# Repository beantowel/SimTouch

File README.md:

# An attempt to make a Capacitive Touch Screen Stimulator

This project attempts to build a device which simulates human finger touch on a capacitive touch screen. We used two high-speed double diodes to build a switch which controls the connection between the conductive surface and the ground. If "the resistance be extremely high and the parasitic capacitance extremely low in the OFF state", then the induced equivalent capacitance would be very small, thus the touch screen won't detect it.

We built an array of these switches in a PCB, so we can use an MCU to control the stimulation in a 2-D plane.

By using PWM, we tried to reach higher resolution with limited conductive pads, since the area of these pads needs to be large to gain enough capacitance.

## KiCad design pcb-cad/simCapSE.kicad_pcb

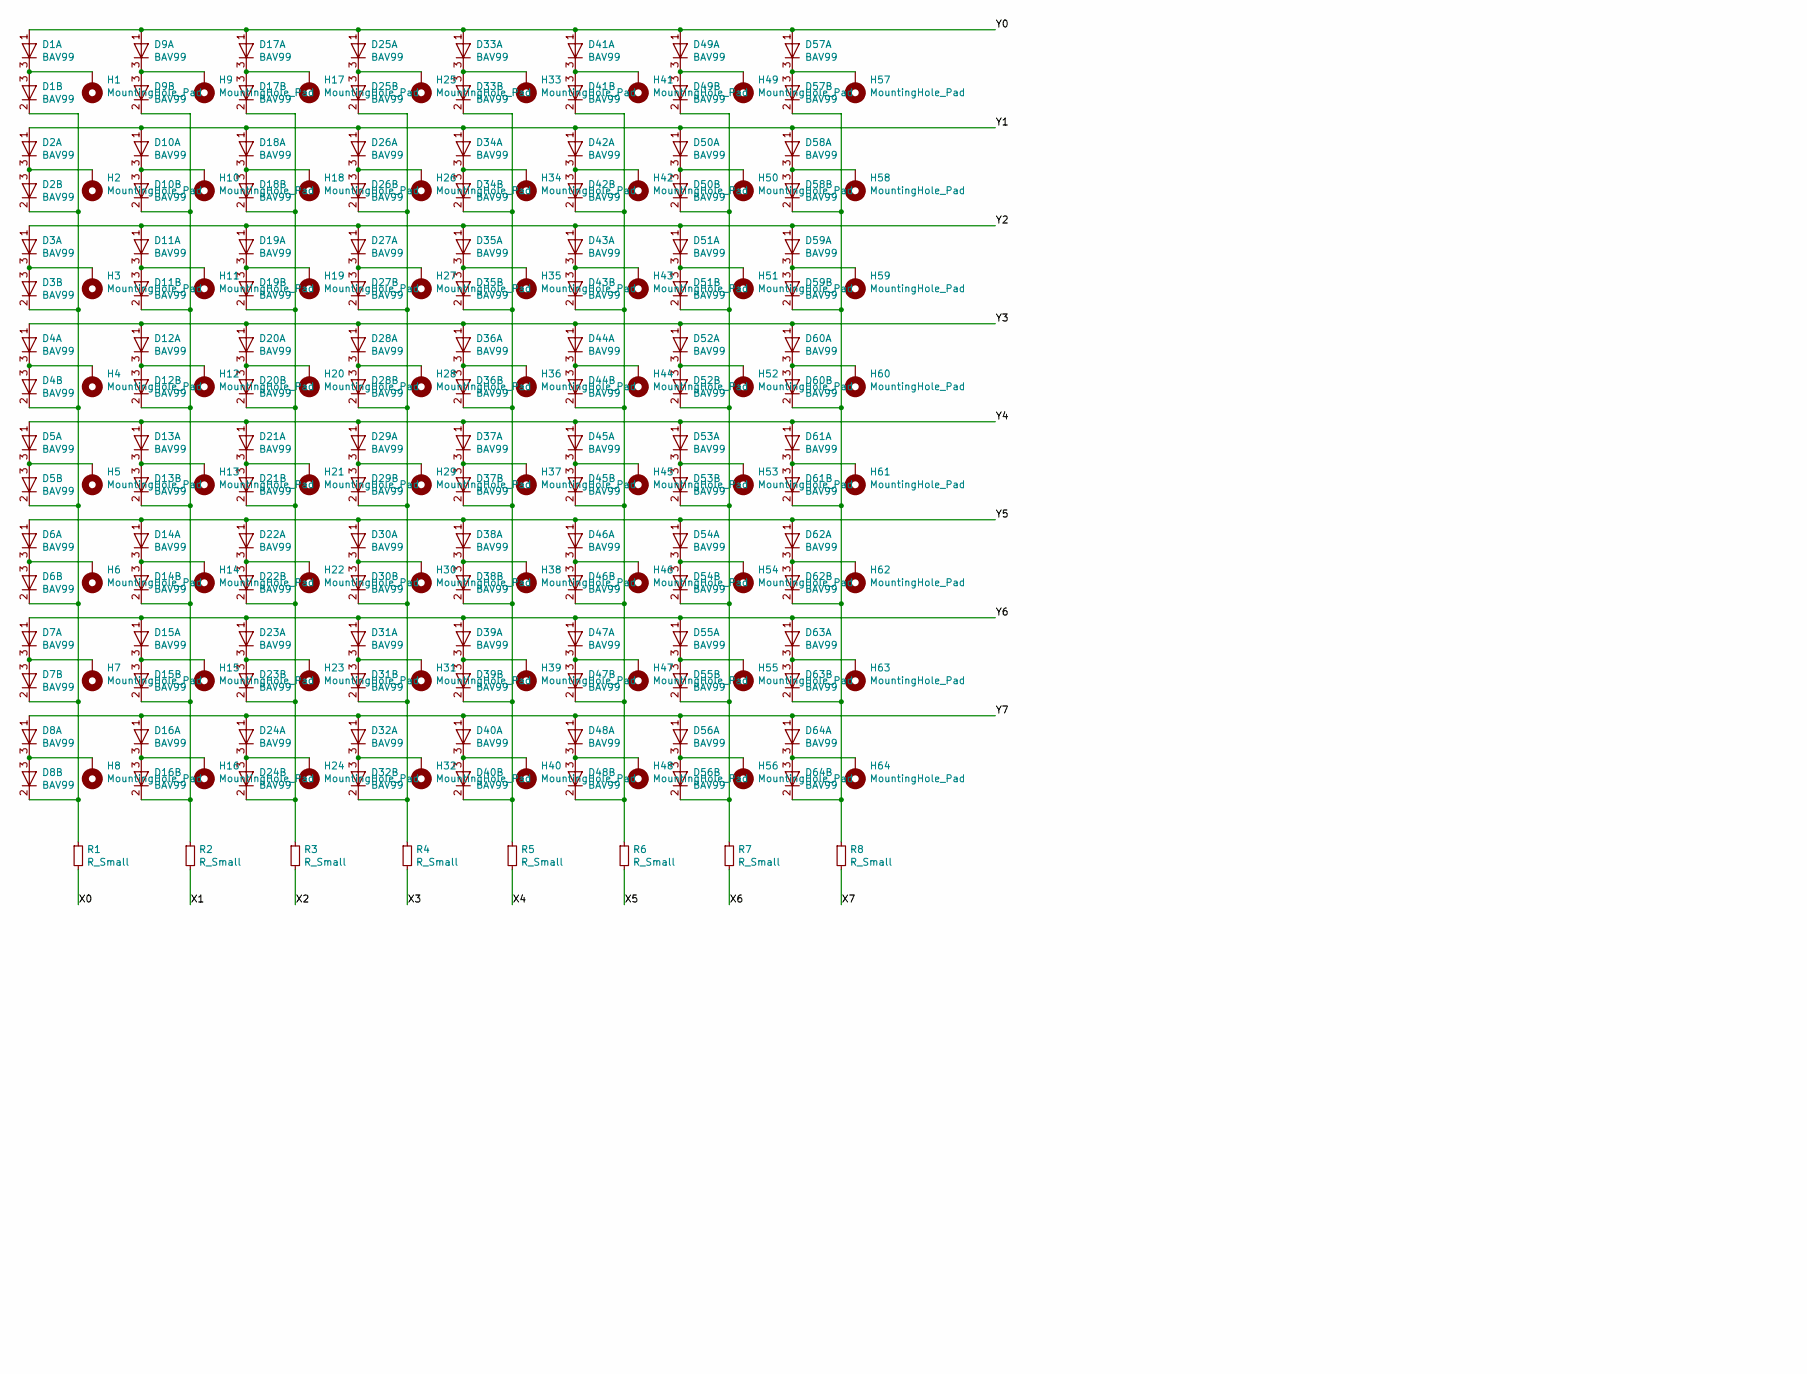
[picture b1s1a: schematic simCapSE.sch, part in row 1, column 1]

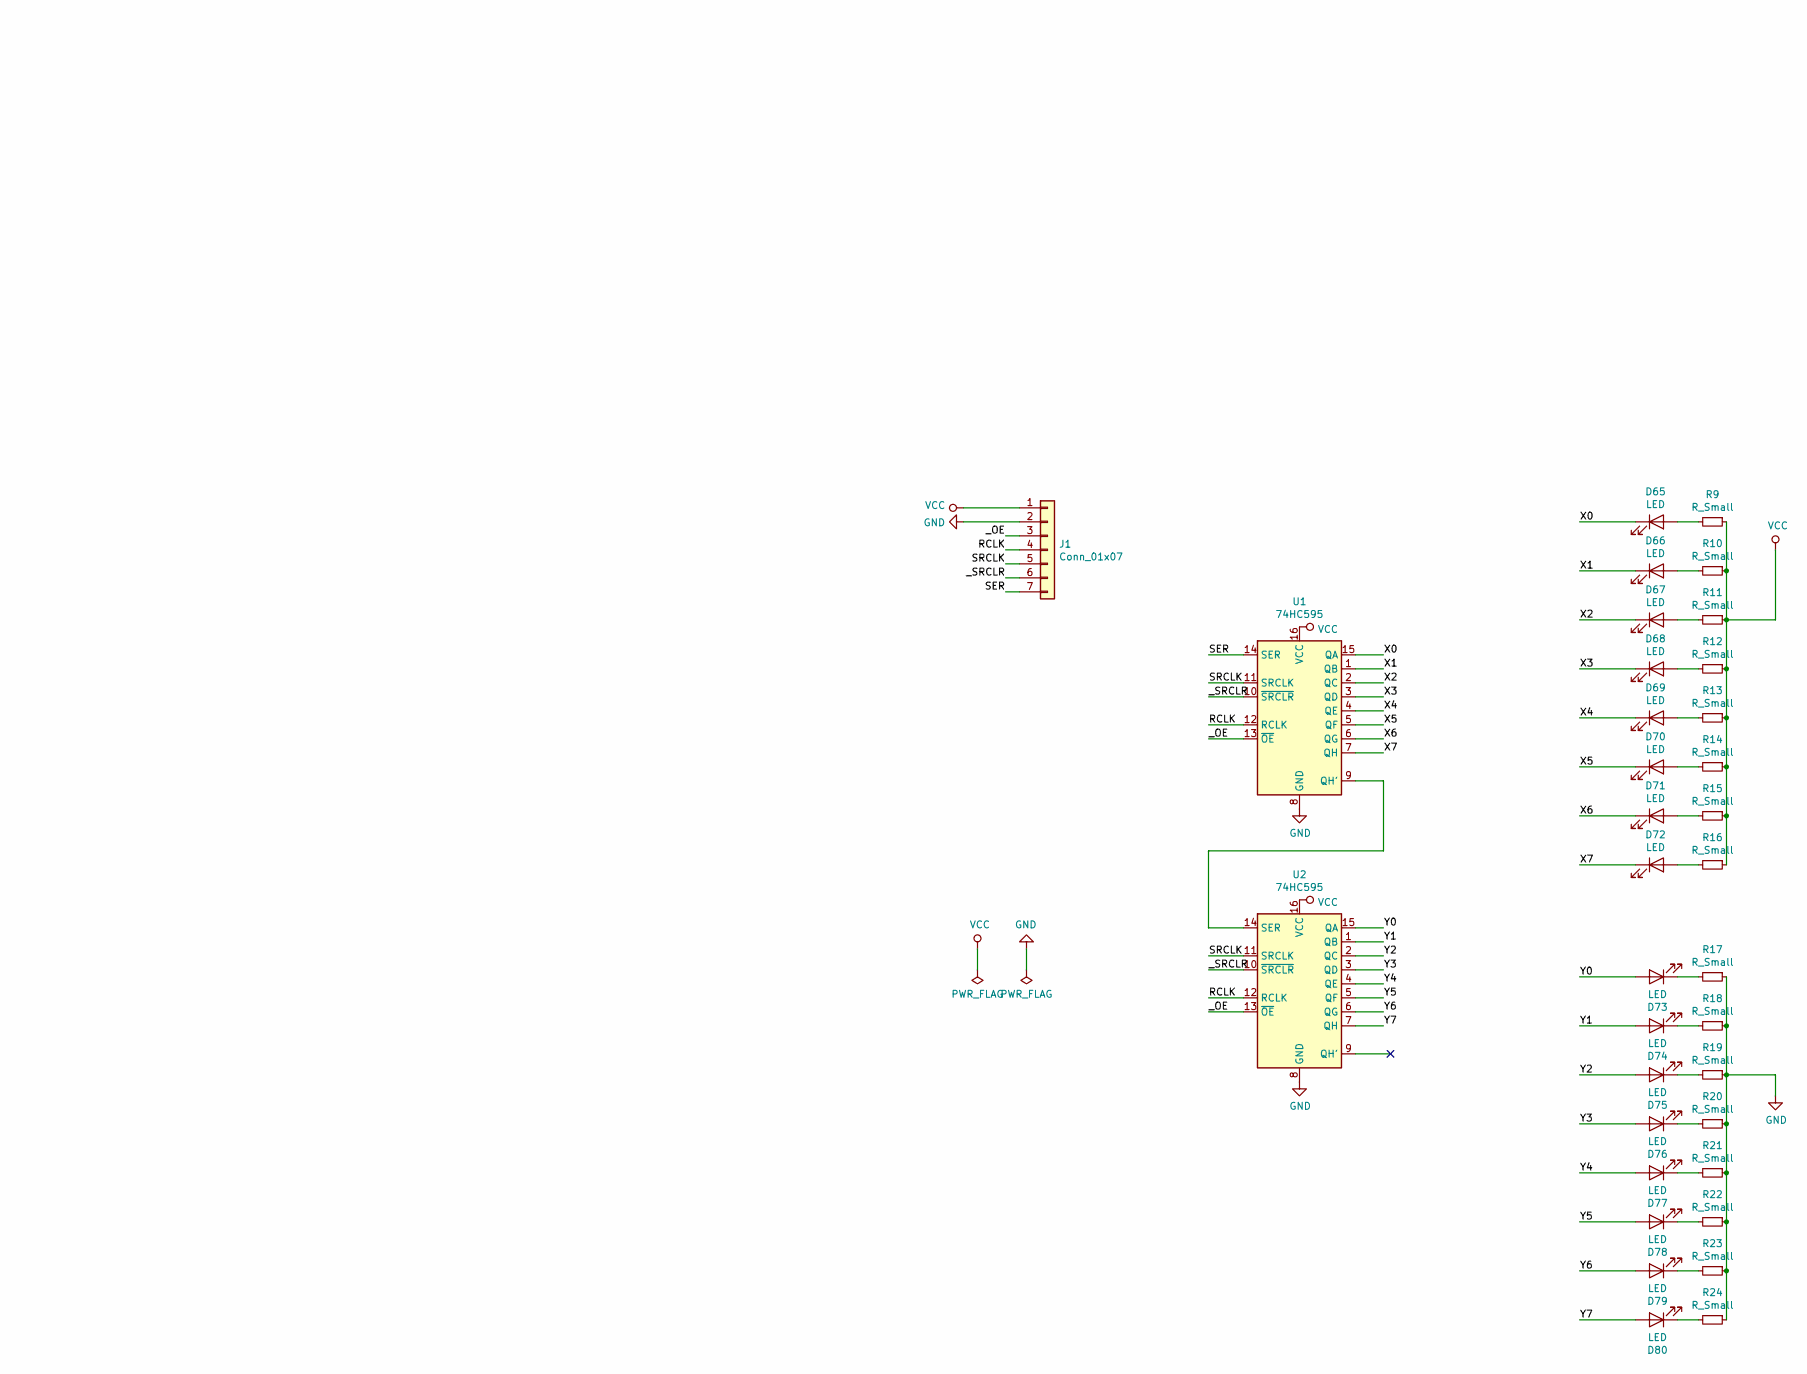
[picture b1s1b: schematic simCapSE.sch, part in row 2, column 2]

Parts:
D1, D2, D3, D4, D5, D6, D7, D8, D9, D10, D11, D12, D13, D14, D15, D16, D17, D18, D19, D20, D21, D22, D23, D24, D25, D26, D27, D28, D29, D30, D31, D32, D33, D34, D35, D36, D37, D38, D39, D40, D41, D42, D43, D44, D45, D46, D47, D48, D49, D50, D51, D52, D53, D54, D55, D56, D57, D58, D59, D60, D61, D62, D63, D64: BAV99; SOT-23
D65, D66, D67, D68, D69, D70, D71, D72, D73, D74, D75, D76, D77, D78, D79, D80: LED; LED_0805_2012Metric_Pad1.15x1.40mm_HandSolder
H1, H2, H3, H4, H5, H6, H7, H8, H9, H10, H11, H12, H13, H14, H15, H16, H17, H18, H19, H20, H21, H22, H23, H24, H25, H26, H27, H28, H29, H30, H31, H32, H33, H34, H35, H36, H37, H38, H39, H40, H41, H42, H43, H44, H45, H46, H47, H48, H49, H50, H51, H52, H53, H54, H55, H56, H57, H58, H59, H60, H61, H62, H63, H64: MountingHole_Pad; TCH_PAD
J1: Conn_01x07; PinHeader_1x07_P2.54mm_Horizontal
R1, R2, R3, R4, R5, R6, R7, R8, R9, R10, R11, R12, R13, R14, R15, R16, R17, R18, R19, R20, R21, R22, R23, R24: R_Small; R_0805_2012Metric_Pad1.15x1.40mm_HandSolder
U1, U2: 74HC595; SOP-16_4.55x10.3mm_P1.27mm

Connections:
/RCLK: J1.4, U1.12 (RCLK), U2.12 (RCLK)
/SER: J1.7, U1.14 (SER)
/SRCLK: J1.5, U1.11 (SRCLK), U2.11 (SRCLK)
/X0: D65.1 (K), R1.2, U1.15 (QA)
/X1: D66.1 (K), R2.2, U1.1 (QB)
/X2: D67.1 (K), R3.2, U1.2 (QC)
/X3: D68.1 (K), R4.2, U1.3 (QD)
/X4: D69.1 (K), R5.2, U1.4 (QE)
/X5: D70.1 (K), R6.2, U1.5 (QF)
/X6: D71.1 (K), R7.2, U1.6 (QG)
/X7: D72.1 (K), R8.2, U1.7 (QH)
/Y0: D1.1 (A), D9.1 (A), D17.1 (A), D25.1 (A), D33.1 (A), D41.1 (A), D49.1 (A), D57.1 (A), D73.2 (A), U2.15 (QA)
/Y1: D2.1 (A), D10.1 (A), D18.1 (A), D26.1 (A), D34.1 (A), D42.1 (A), D50.1 (A), D58.1 (A), D74.2 (A), U2.1 (QB)
/Y2: D3.1 (A), D11.1 (A), D19.1 (A), D27.1 (A), D35.1 (A), D43.1 (A), D51.1 (A), D59.1 (A), D75.2 (A), U2.2 (QC)
/Y3: D4.1 (A), D12.1 (A), D20.1 (A), D28.1 (A), D36.1 (A), D44.1 (A), D52.1 (A), D60.1 (A), D76.2 (A), U2.3 (QD)
/Y4: D5.1 (A), D13.1 (A), D21.1 (A), D29.1 (A), D37.1 (A), D45.1 (A), D53.1 (A), D61.1 (A), D77.2 (A), U2.4 (QE)
/Y5: D6.1 (A), D14.1 (A), D22.1 (A), D30.1 (A), D38.1 (A), D46.1 (A), D54.1 (A), D62.1 (A), D78.2 (A), U2.5 (QF)
/Y6: D7.1 (A), D15.1 (A), D23.1 (A), D31.1 (A), D39.1 (A), D47.1 (A), D55.1 (A), D63.1 (A), D79.2 (A), U2.6 (QG)
/Y7: D8.1 (A), D16.1 (A), D24.1 (A), D32.1 (A), D40.1 (A), D48.1 (A), D56.1 (A), D64.1 (A), D80.2 (A), U2.7 (QH)
/_OE: J1.3, U1.13 (~OE), U2.13 (~OE)
/_SRCLR: J1.6, U1.10 (~SRCLR), U2.10 (~SRCLR)
GND: J1.2, R17.1, R18.1, R19.1, R20.1, R21.1, R22.1, R23.1, R24.1, U1.8 (GND), U2.8 (GND)
unnamed: D1.2 (K), D2.2 (K), D3.2 (K), D4.2 (K), D5.2 (K), D6.2 (K), D7.2 (K), D8.2 (K), R1.1
unnamed: D1.3 (K), H1.1
unnamed: D2.3 (K), H2.1
unnamed: D3.3 (K), H3.1
unnamed: D4.3 (K), H4.1
unnamed: D5.3 (K), H5.1
unnamed: D6.3 (K), H6.1
unnamed: D7.3 (K), H7.1
unnamed: D8.3 (K), H8.1
unnamed: D9.3 (K), H9.1
unnamed: D9.2 (K), D10.2 (K), D11.2 (K), D12.2 (K), D13.2 (K), D14.2 (K), D15.2 (K), D16.2 (K), R2.1
unnamed: D10.3 (K), H10.1
unnamed: D11.3 (K), H11.1
unnamed: D12.3 (K), H12.1
unnamed: D13.3 (K), H13.1
unnamed: D14.3 (K), H14.1
unnamed: D15.3 (K), H15.1
unnamed: D16.3 (K), H16.1
unnamed: D17.2 (K), D18.2 (K), D19.2 (K), D20.2 (K), D21.2 (K), D22.2 (K), D23.2 (K), D24.2 (K), R3.1
unnamed: D17.3 (K), H17.1
unnamed: D18.3 (K), H18.1
unnamed: D19.3 (K), H19.1
unnamed: D20.3 (K), H20.1
unnamed: D21.3 (K), H21.1
unnamed: D22.3 (K), H22.1
unnamed: D23.3 (K), H23.1
unnamed: D24.3 (K), H24.1
unnamed: D25.2 (K), D26.2 (K), D27.2 (K), D28.2 (K), D29.2 (K), D30.2 (K), D31.2 (K), D32.2 (K), R4.1
unnamed: D25.3 (K), H25.1
unnamed: D26.3 (K), H26.1
unnamed: D27.3 (K), H27.1
unnamed: D28.3 (K), H28.1
unnamed: D29.3 (K), H29.1
unnamed: D30.3 (K), H30.1
unnamed: D31.3 (K), H31.1
unnamed: D32.3 (K), H32.1
unnamed: D33.2 (K), D34.2 (K), D35.2 (K), D36.2 (K), D37.2 (K), D38.2 (K), D39.2 (K), D40.2 (K), R5.1
unnamed: D33.3 (K), H33.1
unnamed: D34.3 (K), H34.1
unnamed: D35.3 (K), H35.1
unnamed: D36.3 (K), H36.1
unnamed: D37.3 (K), H37.1
unnamed: D38.3 (K), H38.1
unnamed: D39.3 (K), H39.1
unnamed: D40.3 (K), H40.1
unnamed: D41.2 (K), D42.2 (K), D43.2 (K), D44.2 (K), D45.2 (K), D46.2 (K), D47.2 (K), D48.2 (K), R6.1
unnamed: D41.3 (K), H41.1
unnamed: D42.3 (K), H42.1
unnamed: D43.3 (K), H43.1
unnamed: D44.3 (K), H44.1
unnamed: D45.3 (K), H45.1
unnamed: D46.3 (K), H46.1
unnamed: D47.3 (K), H47.1
unnamed: D48.3 (K), H48.1
unnamed: D49.2 (K), D50.2 (K), D51.2 (K), D52.2 (K), D53.2 (K), D54.2 (K), D55.2 (K), D56.2 (K), R7.1
unnamed: D49.3 (K), H49.1
unnamed: D50.3 (K), H50.1
unnamed: D51.3 (K), H51.1
unnamed: D52.3 (K), H52.1
unnamed: D53.3 (K), H53.1
unnamed: D54.3 (K), H54.1
unnamed: D55.3 (K), H55.1
unnamed: D56.3 (K), H56.1
unnamed: D57.2 (K), D58.2 (K), D59.2 (K), D60.2 (K), D61.2 (K), D62.2 (K), D63.2 (K), D64.2 (K), R8.1
unnamed: D57.3 (K), H57.1
unnamed: D58.3 (K), H58.1
unnamed: D59.3 (K), H59.1
unnamed: D60.3 (K), H60.1
unnamed: D61.3 (K), H61.1
unnamed: D62.3 (K), H62.1
unnamed: D63.3 (K), H63.1
unnamed: D64.3 (K), H64.1
unnamed: D65.2 (A), R9.2
unnamed: D66.2 (A), R10.2
unnamed: D67.2 (A), R11.2
unnamed: D68.2 (A), R12.2
unnamed: D69.2 (A), R13.2
unnamed: D70.2 (A), R14.2
unnamed: D71.2 (A), R15.2
unnamed: D72.2 (A), R16.2
unnamed: D73.1 (K), R17.2
unnamed: D74.1 (K), R18.2
unnamed: D75.1 (K), R19.2
unnamed: D76.1 (K), R20.2
unnamed: D77.1 (K), R21.2
unnamed: D78.1 (K), R22.2
unnamed: D79.1 (K), R23.2
unnamed: D80.1 (K), R24.2
unnamed: U1.9 (QH'), U2.14 (SER)
VCC: J1.1, R9.1, R10.1, R11.1, R12.1, R13.1, R14.1, R15.1, R16.1, U1.16 (VCC), U2.16 (VCC)

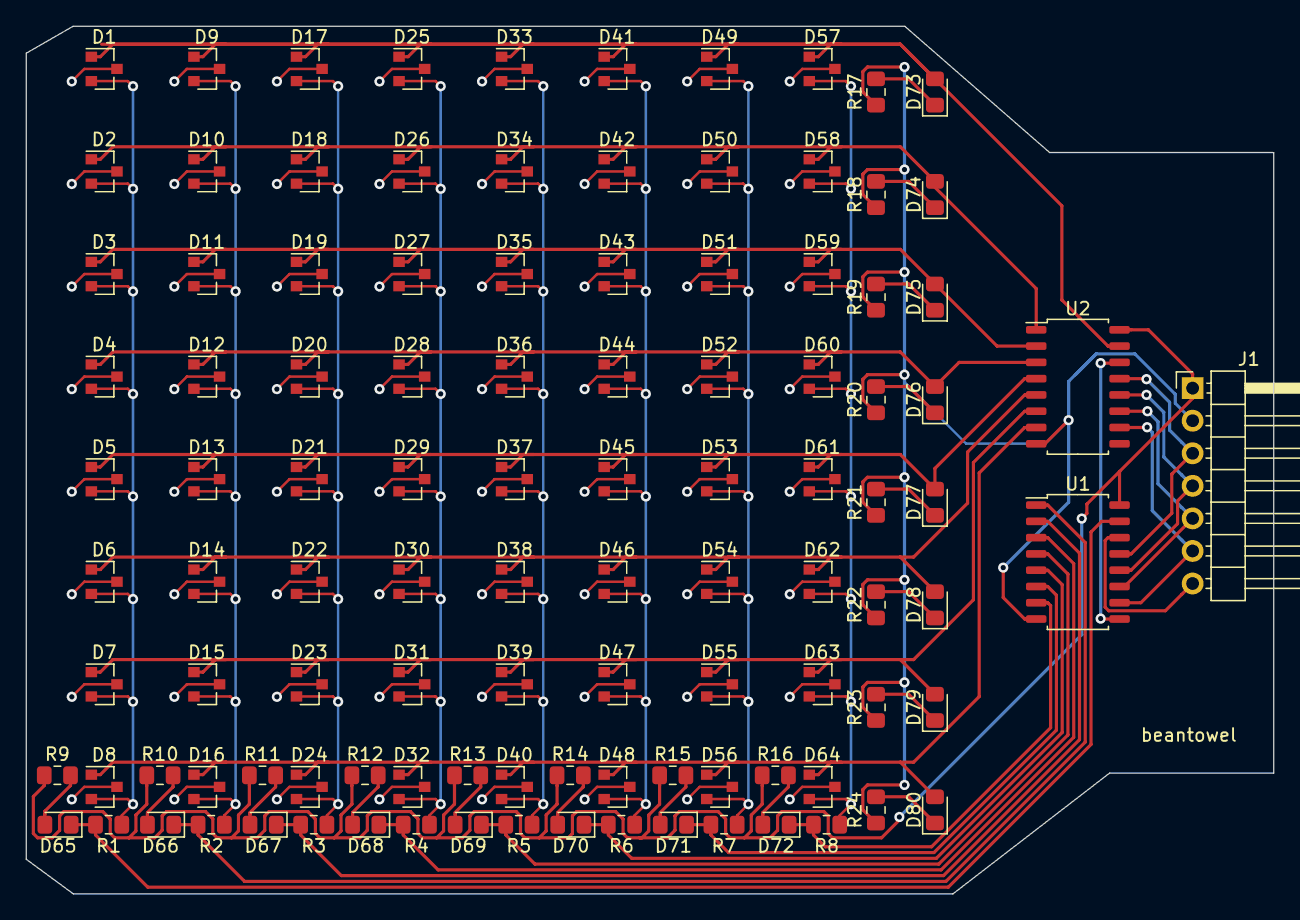
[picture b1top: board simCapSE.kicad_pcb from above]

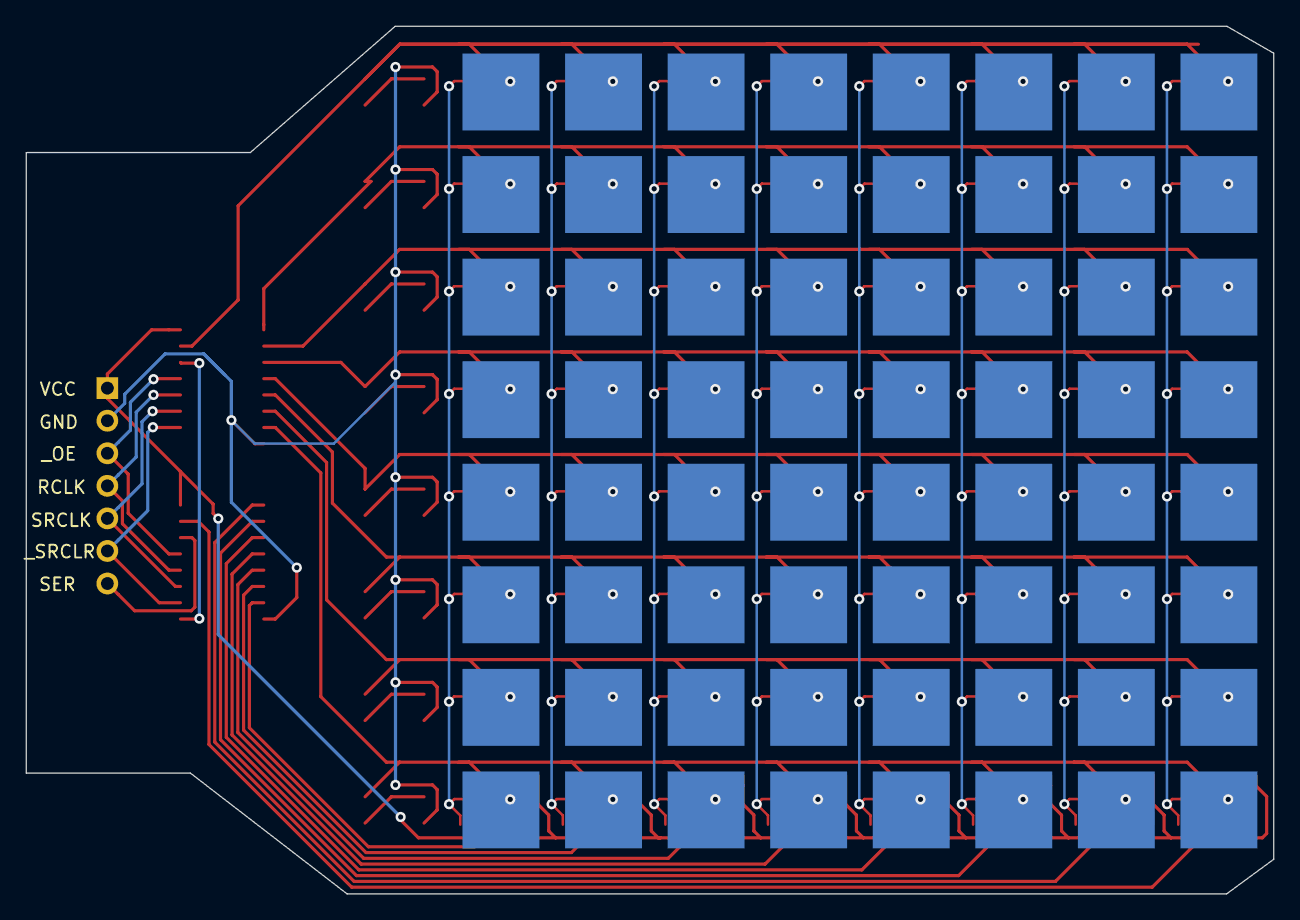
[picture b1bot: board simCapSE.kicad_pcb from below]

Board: 2 copper layers, 97.3 x 67.7 mm, 171 parts (64 on the bottom side), 112 nets.

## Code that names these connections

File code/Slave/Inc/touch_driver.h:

/**
 *
 * Driver for touch simulation
 * control shift register whose output make address of a capacity matrix
 *
 ******************************************************************************
 */

#ifndef __TOUCH_DRIVER__H__
#define __TOUCH_DRIVER__H__

#ifdef __cplusplus
extern "C" {
#endif

#include "stm32f1xx_hal.h"

#define TCHPAD_COLS 8
#define TCHPAD_ROWS 8
#define TCHBOARD_OUTPUT_BUF_SIZE (((TCHPAD_COLS) + (TCHPAD_ROWS)) / 8)

typedef struct _TCH_BOARD {
  // 74HC595 pins
  // 8-Bit Serial-Input/Serial or Parallel-Output ShiftRegister with Latched
  // 3-State Outputs RCLK: latch clock, SRCLK: shiftRegister clock
  GPIO_TypeDef *GPIO_group;
  uint16_t _OE_PIN, RCLK_PIN, SRCLK_PIN, _SRCLR_PIN, SER_PIN;
  uint8_t col_duty, row_duty;
  uint8_t *outputBufHi, *outputBufLo;
} TCH_BOARD;
extern TCH_BOARD tchBoard;

void TCH_Driver_Init(TCH_BOARD *board, GPIO_TypeDef *GPIOx, uint16_t _oe,
                     uint16_t rclk, uint16_t srclk, uint16_t _srclr,
                     uint16_t ser);
uint8_t TCH_Receive_Callback(uint8_t *Buf, uint32_t Len);
void TCH_Start();

#ifdef __cplusplus
}
#endif

#endif /* __TOUCH_DRIVER__H__ */
